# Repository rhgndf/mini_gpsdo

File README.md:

# Mini SI5351 GPSDO

Features
- VC-TCXO at 10MHz
- SI5351 PLL chip, arbitrary frequency output
- All 3 outputs broken out
- STM32G431 microprocessor
- JLCPCB-assembled
- <25USD each
- Designed to fit a 45cm by 45cm by 18.5cm aluminium enclosure.
- Front and back PCB panels coming soon.

## Manufacturing

Obtain the three files in `hardware/jlcpcb/production_files`

- Upload the gerber to the order page, choose SMT assembly
- Upload the BOM and CPL file in the SMT assembly page.

## Firmware

- If the flash is empty, press the BOOT0 button, then the NRST button and release both, if the firmware is already flashed, you can skip this step.
- Run `dfu-util -a 0 -s 0x08000000:leave -D si5351_gpsdo.bin`
  
### Building

Within the `firmware` folder, run
```
cmake -DCMAKE_TOOLCHAIN_FILE=cubeide-gcc.cmake  -S ./ -B Release -G"Unix Makefiles" -DCMAKE_BUILD_TYPE=Release
make -C Release VERBOSE=1 -j
```

## Configuration
The configuration can be done through the web using [https://rhgndf.github.io/mini_gpsdo/](https://rhgndf.github.io/mini_gpsdo/)

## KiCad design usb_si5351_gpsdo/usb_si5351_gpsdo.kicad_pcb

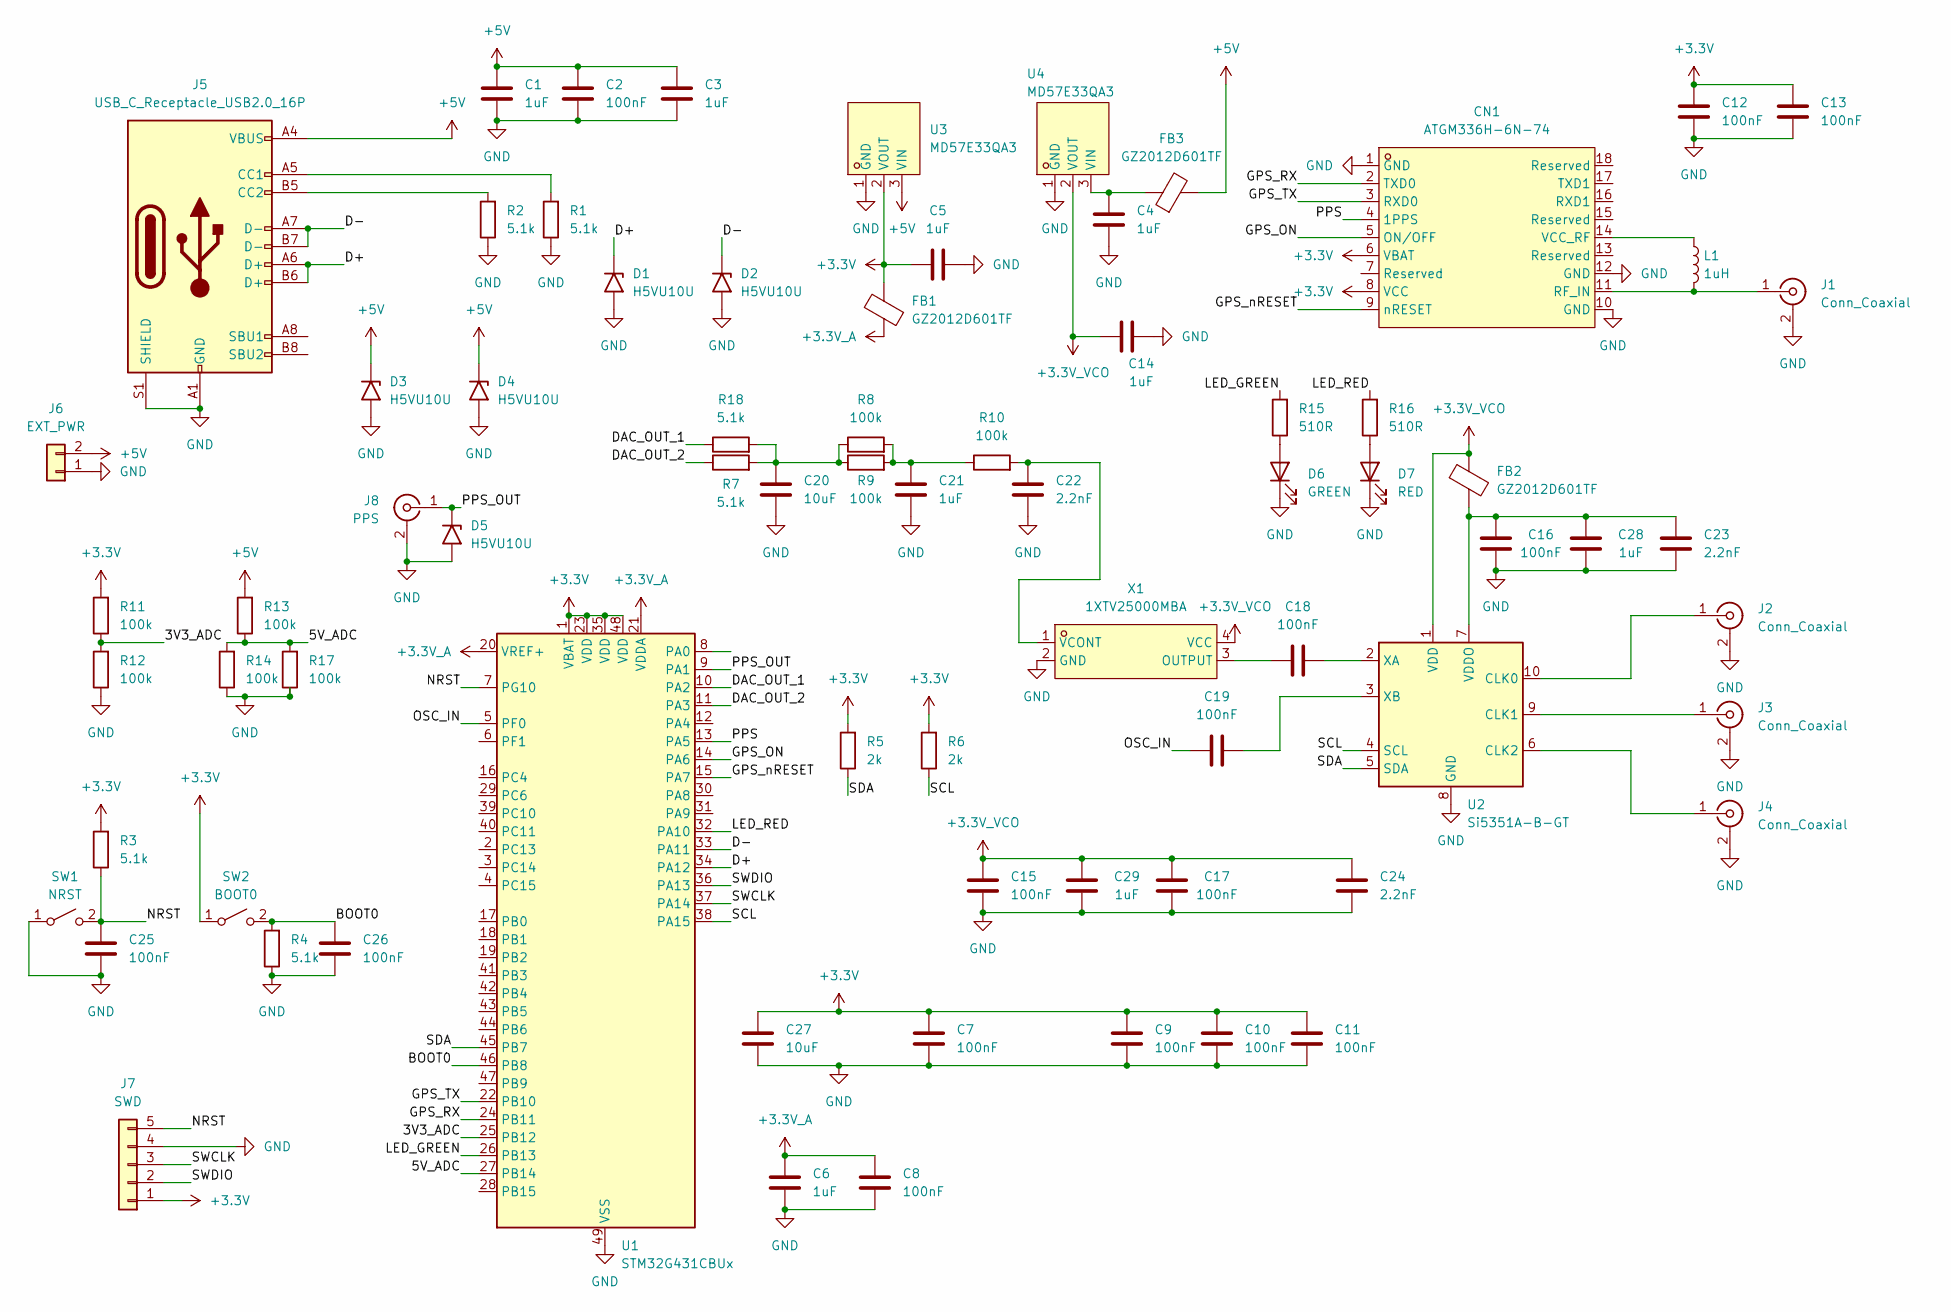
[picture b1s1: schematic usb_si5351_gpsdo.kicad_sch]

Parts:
C1, C3, C4, C5, C6, C14, C21, C28, C29: 1uF; C_0603_1608Metric
C2, C7, C8, C9, C10, C11, C12, C13, C15, C16, C17, C18, C19, C25, C26: 100nF; C_0603_1608Metric
C20, C27: 10uF; C_0603_1608Metric
C22, C23, C24: 2.2nF; C_0805_2012Metric
CN1: ATGM336H-6N-74; COMM-SMD_18P-L10.1-W9.7-P1.1-TL_L76-LB; LCSC Part C5804601
D1, D2, D3, D4, D5: H5VU10U; D_SOD-882D
D6: GREEN; LED_0805_2012Metric
D7: RED; LED_0603_1608Metric
FB1, FB2, FB3: GZ2012D601TF; L_0805_2012Metric
J1, J2, J3, J4: Conn_Coaxial; SMA-SMD_BWSMA-KE-P001
J5: USB_C_Receptacle_USB2.0_16P; USB-C-SMD_TYPE-C16PIN
J6: EXT_PWR; PinHeader_1x02_P2.54mm_Vertical
J7: SWD; PinHeader_1x05_P2.54mm_Vertical
J8: PPS; SMA-SMD_BWSMA-KE-P001
L1: 1uH; L_0805_2012Metric
R1, R2, R3, R4, R7, R18: 5.1k; R_0603_1608Metric
R5, R6: 2k; R_0603_1608Metric
R8, R9, R10, R11, R12, R13, R14, R17: 100k; R_0603_1608Metric
R15, R16: 510R; R_0603_1608Metric
SW1: NRST; SW-SMD_4P-L5.1-W5.1-P3.70-LS6.5-TL-2
SW2: BOOT0; SW-SMD_4P-L5.1-W5.1-P3.70-LS6.5-TL-2
U1: STM32G431CBUx; QFN-48-1EP_7x7mm_P0.5mm_EP5.6x5.6mm
U2: Si5351A-B-GT; MSOP-10_3x3mm_P0.5mm
U3, U4: MD57E33QA3; SOT-23-3_L2.9-W1.6-P1.90-LS2.8-BR; LCSC Part C920553
X1: 1XTV25000MBA; OSC-SMD_4P-L3.2-W2.5-BL; LCSC Part C253674

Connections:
+3.3V: C5.1, C7.1, C9.1, C10.1, C11.1, C12.1, C13.1, C27.1, CN1.6 (VBAT), CN1.8 (VCC), FB1.2, J7.1, R3.2, R5.2, R6.2, R11.2, SW2.1 (A), U1.1 (VBAT), U1.23 (VDD), U1.35 (VDD), U1.48 (VDD), U3.2 (VOUT)
+3.3V_A: C6.1, C8.1, FB1.1, U1.20 (VREF+), U1.21 (VDDA)
+3.3V_VCO: C14.1, C15.1, C17.2, C24.1, C29.1, FB2.1, U2.1 (VDD), U4.2 (VOUT), X1.4 (VCC)
+5V: C1.1, C2.1, C3.1, D3.1 (A1), D4.1 (A1), FB3.2, J5.A4 (VBUS), J5.A9 (VBUS), J5.B4 (VBUS), J5.B9 (VBUS), J6.2, R13.2, U3.3 (VIN)
/3V3_ADC: R11.1, R12.2, U1.25 (PB12)
/5V_ADC: R13.1, R14.2, R17.2, U1.27 (PB14)
/BOOT0: C26.2, R4.2, SW2.2 (B), U1.46 (PB8)
/D+: D1.1 (A1), J5.A6 (D+), J5.B6 (D+), U1.34 (PA12)
/D-: D2.1 (A1), J5.A7 (D-), J5.B7 (D-), U1.33 (PA11)
/DAC_OUT_1: R18.1, U1.10 (PA2)
/DAC_OUT_2: R7.1, U1.11 (PA3)
/GPS_ON: CN1.5 (ON/OFF), U1.14 (PA6)
/GPS_RX: CN1.2 (TXD0), U1.24 (PB11)
/GPS_TX: CN1.3 (RXD0), U1.22 (PB10)
/GPS_nRESET: CN1.9 (nRESET), U1.15 (PA7)
/LED_GREEN: R15.2, U1.26 (PB13)
/LED_RED: R16.2, U1.32 (PA10)
/NRST: C25.2, J7.5, R3.1, SW1.2 (B), U1.7 (PG10)
/OSC_IN: C19.1, U1.5 (PF0)
/PPS: CN1.4 (1PPS), U1.13 (PA5)
/PPS_OUT: D5.1 (A1), J8.1 (In), U1.9 (PA1)
/SCL: R6.1, U1.38 (PA15), U2.4 (SCL)
/SDA: R5.1, U1.45 (PB7), U2.5 (SDA)
/SWCLK: J7.3, U1.37 (PA14)
/SWDIO: J7.2, U1.36 (PA13)
GND: C1.2, C2.2, C3.2, C4.2, C5.2, C6.2, C7.2, C8.2, C9.2, C10.2, C11.2, C12.2, C13.2, C14.2, C15.2, C16.2, C17.1, C20.2, C21.2, C22.2, C23.2, C24.2, C25.1, C26.1, C27.2, C28.2, C29.2, CN1.1 (GND), CN1.10 (GND), CN1.12 (GND), D1.2 (A2), D2.2 (A2), D3.2 (A2), D4.2 (A2), D5.2 (A2), D6.1 (K), D7.1 (K), J1.2 (Ext), J2.2 (Ext), J3.2 (Ext), J4.2 (Ext), J5.A1 (GND), J5.A12 (GND), J5.B1 (GND), J5.B12 (GND), J5.S1 (SHIELD), J6.1, J7.4, J8.2 (Ext), R1.1, R2.1, R4.1, R12.1, R14.1, R17.1, SW1.1 (A), U1.49 (VSS), U2.8 (GND), U3.1 (GND), U4.1 (GND), X1.2 (GND)
unnamed: C20.1, R7.2, R8.1, R9.1, R18.2
unnamed: C21.1, R8.2, R9.2, R10.1
unnamed: CN1.11 (RF_IN), J1.1 (In), L1.2
unnamed: CN1.14 (VCC_RF), L1.1
unnamed: D6.2 (A), R15.1
unnamed: D7.2 (A), R16.1
unnamed: J2.1 (In), U2.10 (CLK0)
unnamed: J3.1 (In), U2.9 (CLK1)
unnamed: J4.1 (In), U2.6 (CLK2)
unnamed: J5.A5 (CC1), R1.2
unnamed: J5.B5 (CC2), R2.2
unnamed: C16.1, C23.1, C28.1, FB2.2, U2.7 (VDDO)
unnamed: C18.2, U2.2 (XA)
unnamed: C19.2, U2.3 (XB)
unnamed: C4.1, FB3.1, U4.3 (VIN)
unnamed: C18.1, X1.3 (OUTPUT)
unnamed: C22.1, R10.2, X1.1 (VCONT)

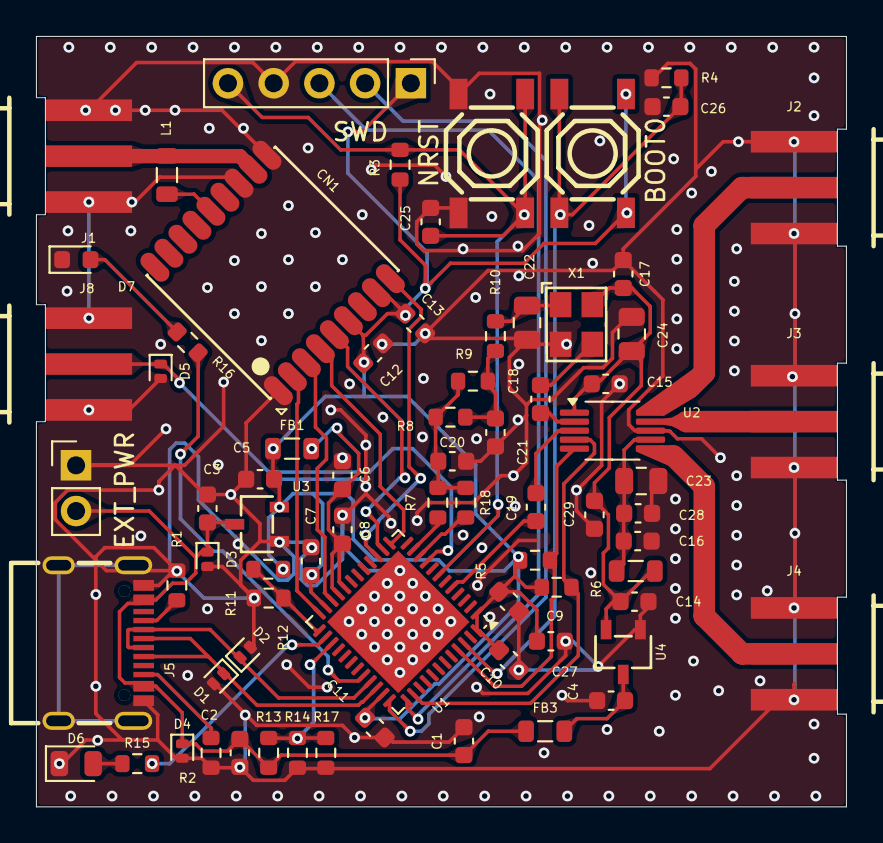
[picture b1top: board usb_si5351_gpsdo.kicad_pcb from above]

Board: 2 copper layers, 45.0 x 42.8 mm, 74 parts (0 on the bottom side), 43 nets.

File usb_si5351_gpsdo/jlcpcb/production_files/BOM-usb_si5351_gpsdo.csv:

Comment,Designator,Footprint,LCSC
GZ2012D601TF,"FB1,FB2,FB3",L_0805_2012Metric,C1017
1uH,L1,L_0805_2012Metric,C1042
100nF,"C10,C11,C12,C13,C15,C16,C17,C18,C19,C2,C25,C26,C7,C8,C9",C_0603_1608Metric,C14663
Si5351A-B-GT,U2,MSOP-10_3x3mm_P0.5mm,C1509083
1uF,"C1,C14,C21,C28,C29,C3,C4,C5,C6",C_0603_1608Metric,C15849
H5VU10U,"D1,D2,D3,D4,D5",D_SOD-882D,C22395519
RED,D7,LED_0603_1608Metric,C2286
GREEN,D6,LED_0805_2012Metric,C2297
2k,"R5,R6",R_0603_1608Metric,C22975
5.1k,"R1,R18,R2,R3,R4,R7",R_0603_1608Metric,C23186
510R,"R15,R16",R_0603_1608Metric,C23193
1XTV25000MBA,X1,OSC-SMD_4P-L3.2-W2.5-BL,C253701
100k,"R10,R11,R12,R13,R14,R17,R8,R9",R_0603_1608Metric,C25803
USB_C_Receptacle_USB2.0_16P,J5,USB-C-SMD_TYPE-C16PIN,C2765186
2.2nF,"C22,C23,C24",C_0805_2012Metric,C28260
NRST,"SW1,SW2",SW-SMD_4P-L5.1-W5.1-P3.70-LS6.5-TL-2,C318884
STM32G431CBUx,U1,QFN-48-1EP_7x7mm_P0.5mm_EP5.6x5.6mm,C529356
ATGM336H-6N-74,CN1,COMM-SMD_18P-L10.1-W9.7-P1.1-TL_L76-LB,C5804601
MD57E33QA3,"U3,U4",SOT-23-3_L2.9-W1.6-P1.90-LS2.8-BR,C920553
10uF,"C20,C27",C_0603_1608Metric,C96446
PPS,J8,SMA-SMD_BWSMA-KE-P001,
Conn_Coaxial,J2,SMA-SMD_BWSMA-KE-P001,
Conn_Coaxial,J1,SMA-SMD_BWSMA-KE-P001,
SWD,J7,PinHeader_1x05_P2.54mm_Vertical,
EXT_PWR,J6,PinHeader_1x02_P2.54mm_Vertical,
Conn_Coaxial,J4,SMA-SMD_BWSMA-KE-P001,
Conn_Coaxial,J3,SMA-SMD_BWSMA-KE-P001,

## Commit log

2024-10-19 code
2024-11-09 Initial full commit
2024-11-09 Add git submodules
2024-11-09 Add github actions
2024-11-09 Use relative paths
2024-11-09 Add README
